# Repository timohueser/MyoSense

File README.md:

# MyoSense
## Overview
MyoSense is a armband designed to wirelessly track and interpret muscle activity in the forearm to predict handmovements. It uses a custom designed 2.4GHz interface to transmit the signals collected by up to eight sensors to a receiver that can be read out over a standard serial interface. The armband uses dry stainless steel electrodes incorporated into the sensor modules that can pick up the electromygraphic signal generated by muscle activity. Using external adhesive electrodes that can be attached to each sensor MyoSense is also able to read out activity of bigger muscles extendig it's possible usecases to tracking movements of all extremities. 

## Technical Details
### Sensor Modules

As mentioned before the MyoSense Sensor Modules use dry stainless steel electrodes to pick up the small voltages generated by muscle activity on the skin above the monitored muscle. These voltages get amplified, bandpass-filtered and rectified using analog circuitry. It should be noted that filtering includes a 50Hz mains frequence notch filter, since the body picks this noise up very strongly. After the rectification the signal gets smoothed, or averaged, by a lowpass filter stage. This results in a DC voltage level that is proportional to the strength of muscle activity. Smoothing the signal has the advantage to be able to sample it at very low frequencies, On the other hand Information that could be extracted from the frequency of the EMG śignal, like the level of muscle fatigue is lost. 

The processed signal gets digitized by an Attiny85 microcontroller that in turn uses an I2C interface to send the measured voltages to the control module. A push-button on the sensor allows the user to set the I2C adress of the module, allowing up to eight sensors to be used with one control module. The modules consist of a custom design PCB, 3 stainless steel plates serving as the electrodes and a 3D-printed housing. The Kicad design files for the PCB and STL files of the housing can be found in the repository. 

### Control Module
The control module not only is responsible for reading out the senors and transmitting the collected data via a 2.4GHz interfaceto the receiver unit described below, it also contains circuitry to charge a 250 mAh Lipo Battery and supply the requiered 3V and -3V power rails to the sensor modules. In addition it also contains a MCP2221 I2C/UART to USB interface IC enabling direct wired acces to the I2C bus through the same Micro-USB port that is used for charging. 
The wireless communication module used is custom designed and uses the Nordic Semi nRF24L01 2.4GHz transciever IC controlled by an Attiny85 mircrocontroller that also controlls the sensors over the I2C bus. Both the control and the sensor modules can be reprogrammed using the ICSP compatible connector that is also used to connect them with eachother. 

### Wireless receiver and GUI

The wireless receiver also uses the nRF24L01 transciever and Attiny85 microcontroller as the transmitter module. The microcontroller then connects to another MCP2221 USB interface IC to be able to transmit the received data to a computer over a standard serial interface. The repository also contains an UI-Program implementet in c++ using QT that allows easy access to the receiver module and visualizes the data collected. The repository also contains a python script that implements a neural network that can be used to classify different movement patterns. At the moment this functionality is not available in the GUI, but it is planned to integrate this feature.

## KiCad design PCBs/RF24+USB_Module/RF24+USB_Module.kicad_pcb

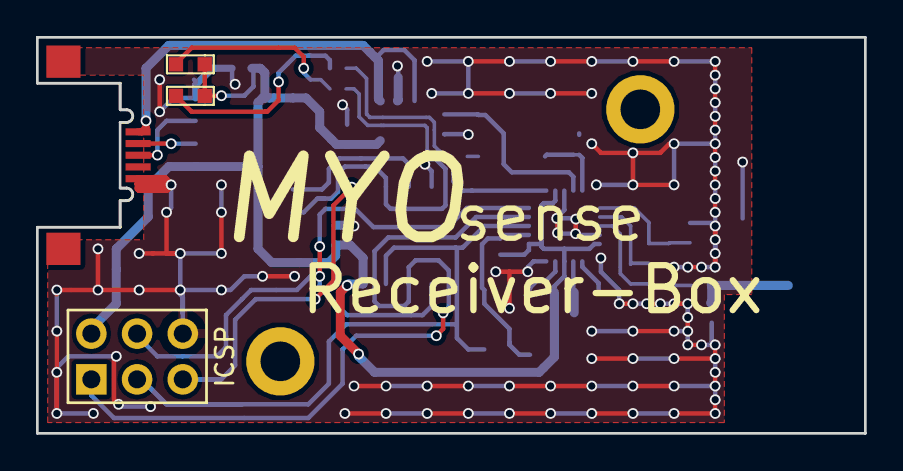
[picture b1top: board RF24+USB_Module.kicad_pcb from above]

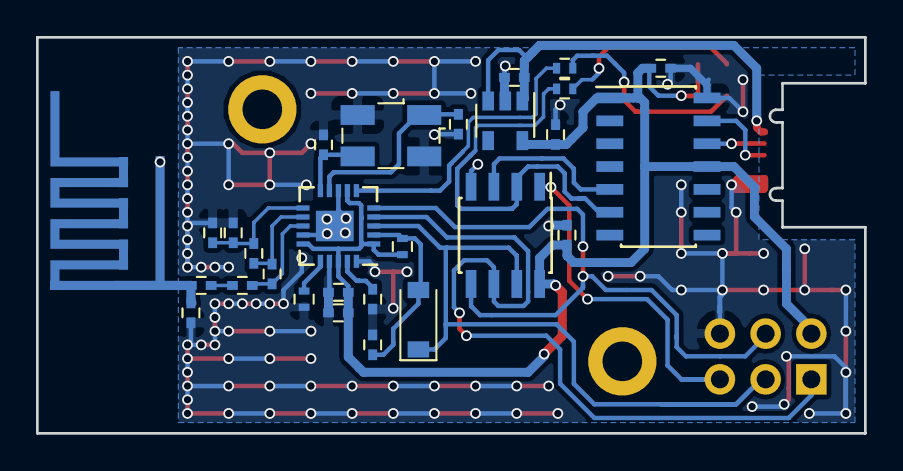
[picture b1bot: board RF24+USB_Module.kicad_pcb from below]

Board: 2 copper layers, 46.0 x 22.0 mm, 32 parts (29 on the bottom side), 24 nets.

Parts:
AE1: Antenna_Dipole; MIFA-Antenna
C1, C4, C12: 100nF; C_0402
C2: 33nF; C_0402
C3: 1uF; C_0402
C5: 10nF; C_0402
C6: 1.5pF; C_0402
C7: 1.0pF; C_0402
C8: 2.2pF; C_0402
C9: 4.7pF; C_0402
C10, C11: 22pF; C_0402
C13, C14: C_Small; C_0402
D1: 1N4148; D_SOD-123
D2, D3: LED_Small; LED_0603
J1: CONN_01X05; Micro_B_Conrad
J2: ICSP; Socket_Strip_Straight_2x03_Pitch2.54mm
L1: 3.9nH; C_0402
L2: 8.2nH; C_0402
L3: 2.7nH; C_0402
R1: 22k; R_0402
R2: 4.7k; R_0402
R3, R4: R_Small; R_0402
U1: ATTINY85-20SU; SOIC-8_3.9x4.9mm_Pitch1.27mm
U2: nRF24l01+; QFN-20-1EP_4x4mm_Pitch0.5mm
U3: MCP2221; SOIC-14_3.9x8.7mm_Pitch1.27mm
U4: MIC5504; SOT-23-5
Y1: Crystal_GND24; Crystal_SMD_EuroQuartz_MJ-4pin_5.0x3.2mm

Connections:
GND: AE1.2, C1.2, C2.2, C3.2, C4.2, C5.2, C7.2, C8.2, C9.2, C10.2, C11.2, C12.1, C13.2, C14.2, J1.5, J2.6, R1.1, U1.4, U2.8, U2.14, U2.17, U2.20, U3.14, U4.2, Y1.2, Y1.4
IRQ: R3.2, U2.6
MISO: J2.1, U1.6, U2.4
MOSI: J2.4, U1.5, U2.5
unnamed: AE1.1, C6.1, C7.1
unnamed: C2.1, U2.19
unnamed: C5.1, D1.2, R2.2, U2.2
unnamed: C6.2, L1.2
unnamed: C8.1, C9.1, L3.1, U2.11
unnamed: C10.1, U2.9, Y1.1
unnamed: C11.1, U2.10, Y1.3
unnamed: D2.1, R3.1
unnamed: D3.1, R4.1
unnamed: J1.2, U3.12
unnamed: J1.3, U3.13
unnamed: L1.1, L2.1, U2.13
unnamed: L2.2, L3.2, U2.12
unnamed: R1.2, U2.16
RST: J2.5, U1.1
Rx: U1.3, U3.5
SCK: D1.1, J2.3, U1.7, U2.3
Tx: R4.2, U1.2, U3.6
VCC: C1.1, C3.1, C4.1, C12.2, C14.1, D2.2, D3.2, J2.2, R2.1, U1.8, U2.1, U2.7, U2.15, U2.18, U3.1, U3.11, U4.5
V_USB: C13.1, J1.1, U4.1, U4.3

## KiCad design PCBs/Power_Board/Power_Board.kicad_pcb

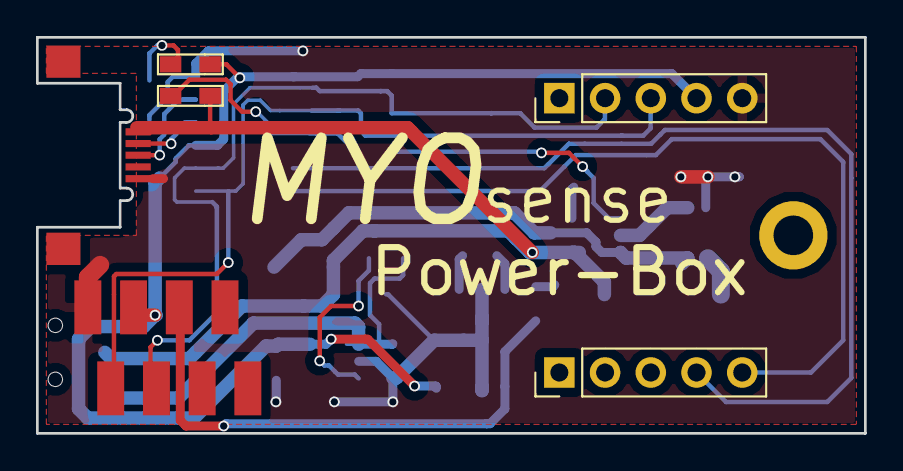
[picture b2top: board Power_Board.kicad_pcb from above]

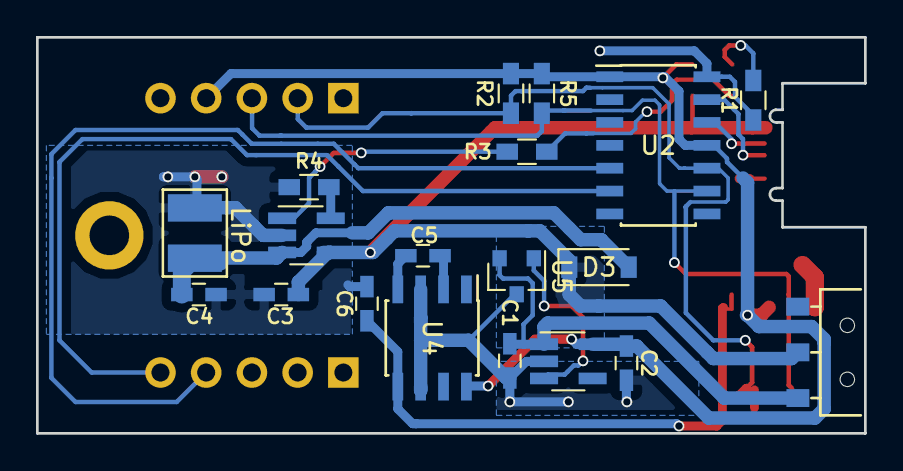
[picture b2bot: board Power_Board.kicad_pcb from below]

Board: 2 copper layers, 46.0 x 22.0 mm, 25 parts (19 on the bottom side), 19 nets.

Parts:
C1, C2: 1uF; C_0603_HandSoldering
C3, C4: 4.7uF; C_0603_HandSoldering
C5, C6: C; C_0603_HandSoldering
D1, D2: LED; LED_0603_HandSoldering
D3: MBR120; D_SOD-123
J2: LIPO; LiPo_Conn
J3: CONN_02X04; Micro_Match_02x04
J4: CONN_01X05; Micro_B_Conrad
J5, J6: CONN_01X05; Socket_Strip_Straight_1x05_Pitch2.54mm
R1, R2, R3, R4, R5: R; R_0603_HandSoldering
SW1: SW_DPDT_x2; slide_switch_conrad
U1: MIC5504; SOT-23-5_HandSoldering
U2: MCP2221; SOIC-14_3.9x8.7mm_Pitch1.27mm
U3: MCP73832; SOT-23-5_HandSoldering
U4: Lm2660; SOIC-8_3.9x4.9mm_Pitch1.27mm
U5: MCP100T; SOT-23

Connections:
GND: C1.2, C2.2, C3.2, C4.2, C6.2, J2.1, J3.7, J4.5, J5.5, R1.2, R4.2, U1.2, U2.14, U3.2, U4.3, U4.6, U5.3
LIPO_POS: C4.1, D3.2, J2.2, U3.3
unnamed: C1.1, SW1.1, U1.1, U5.2
unnamed: C5.1, U4.2
unnamed: C5.2, U4.4
unnamed: D1.1, R1.1
unnamed: D2.1, R3.1
unnamed: J4.2, U2.12
unnamed: J4.3, U2.13
unnamed: R3.2, U3.1
unnamed: R4.1, U3.5
unnamed: U1.3, U5.1
Rx: J6.4, U2.5
SCL: J3.6, J5.2, R2.2, U2.10
SDA: J3.8, J5.3, R5.2, U2.9
Tx: J6.5, U2.6
USB_Vin: C3.1, D2.2, D3.1, J4.1, SW1.2, U3.4
VCC: C2.1, D1.2, J3.5, J5.4, R2.1, R5.1, U1.5, U2.1, U2.11, U4.8
VSS: C6.1, J3.3, U4.5

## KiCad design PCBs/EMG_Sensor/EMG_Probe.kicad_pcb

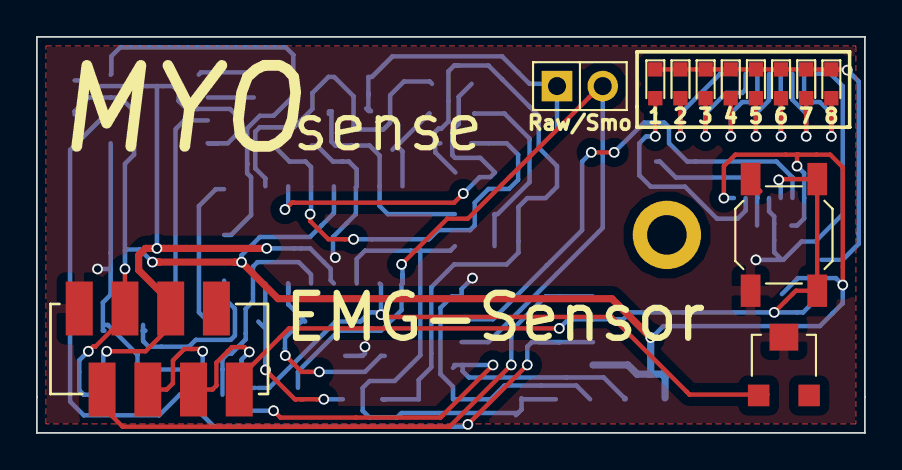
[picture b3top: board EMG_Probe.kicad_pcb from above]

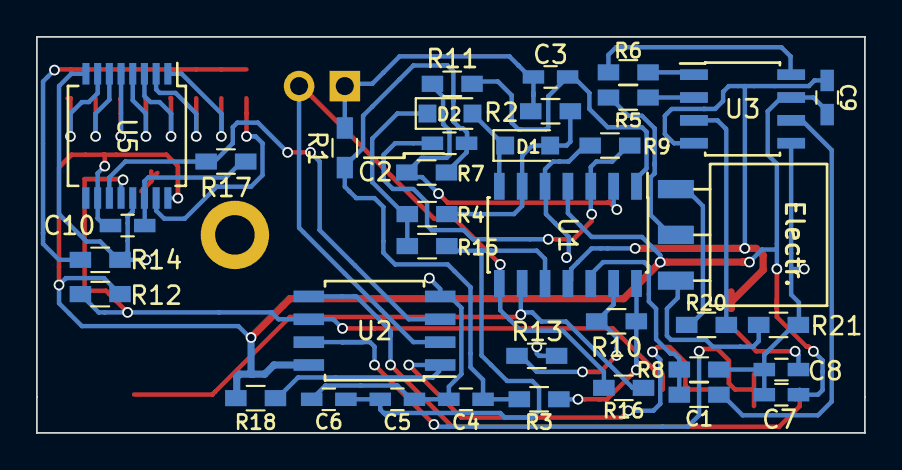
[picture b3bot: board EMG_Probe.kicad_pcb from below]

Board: 2 copper layers, 46.0 x 22.0 mm, 49 parts (37 on the bottom side), 40 nets.

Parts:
C1: 220n; R_0603_HandSoldering
C2, C3: 47n; C_0603_HandSoldering
C4, C5, C6: 220n; C_0603_HandSoldering
C7, C8, C9, C10: 100n; C_0603_HandSoldering
D1, D2: D; D_SOD-323_HandSoldering
D3, D4, D5, D6, D7, D8, D9, D10: LED; LED_0603
J1: Sensor_Connect; Header_Angled_03
P1: CONN_01X02; Pin_Header_Straight_1x02_Pitch2.54mm
P2: CONN_02X04; Micro_Match_02x04
R1, R9: 68k; R_0603_HandSoldering
R2: 22k; R_0603_HandSoldering
R3, R13: 2k2; R_0603_HandSoldering
R4, R5, R8, R10, R15, R16, R20, R21: 100k; R_0603_HandSoldering
R6: 1.5k; R_0603_HandSoldering
R7, R11, R12, R18: 10k; R_0603_HandSoldering
R14: R; R_0603_HandSoldering
R17: 1k5; R_0603_HandSoldering
RV1: POT; Potentiometer_Trimmer-EVM3E
SW2: SW_PUSH; SW_SPST_SKQG
U1: TLV274; SOIC-14_3.9x8.7mm_Pitch1.27mm
U2: ATTINY85-20SU; SOIJ-8_5.3x5.3mm_Pitch1.27mm
U3: INA126; SOIC-8_3.9x4.9mm_Pitch1.27mm
U5: 74HC595; SSOP-16_5.3x6.2mm_Pitch0.65mm

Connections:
Ard_Output: P1.2, R16.1, U1.8, U2.2
GND: C4.1, C5.2, C6.2, C7.1, C8.1, P2.7, R8.2, R9.2, R13.2, R14.2, R21.2, RV1.2, SW2.1, U1.5, U2.4, U3.5, U5.8, U5.13
unnamed: C1.1, R8.1, U1.12
unnamed: C1.2, U3.6
unnamed: C2.1, C4.2, R1.2, R3.1, R7.2
unnamed: C2.2, R9.1, U1.3
unnamed: C3.2, R11.1, U1.1
unnamed: C5.1, C6.1, R15.1, U1.10
unnamed: C10.2, R17.1, U5.14
unnamed: D1.1, D2.2, U1.7
unnamed: D1.2, R2.1, R4.2, U1.6
unnamed: D3.2, U5.15
unnamed: D4.2, U5.1
unnamed: D5.2, U5.2
unnamed: D6.2, U5.3
unnamed: D7.2, U5.4
unnamed: D8.2, U5.5
unnamed: D9.2, U5.6
unnamed: D3.1, D4.1, D5.1, D6.1, D7.1, D8.1, D9.1, D10.1, R14.1
unnamed: D10.2, U5.7
unnamed: J1.1, R5.2
unnamed: J1.2, R20.2
unnamed: J1.3, R21.1
unnamed: P2.2, R12.1, SW2.2, U2.6, U5.12
unnamed: P2.4, R18.1, U2.1
unnamed: R5.1, U3.2
unnamed: R6.1, U3.8
unnamed: R6.2, U3.1
unnamed: R3.2, R10.1, U1.14
unnamed: R10.2, R13.1, U1.13
unnamed: R7.1, R11.2, U1.2
unnamed: R16.2, RV1.1, U1.9
unnamed: R17.2, U2.3, U5.11
unnamed: R20.1, U3.3
Raw_Output: C3.1, P1.1, R1.1, R2.2
SCL: P2.6, U2.7
SDA: P2.8, U2.5
Signal: D2.1, R4.1, R15.2
VCC: C7.2, C9.2, C10.1, P2.5, R12.2, R18.2, U1.4, U2.8, U3.7, U5.10, U5.16
VSS: C8.2, C9.1, P2.3, U1.11, U3.4

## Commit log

2019-01-11 Create LICENSE
